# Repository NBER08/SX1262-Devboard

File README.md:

# SX1262 devboard for LoRa testing

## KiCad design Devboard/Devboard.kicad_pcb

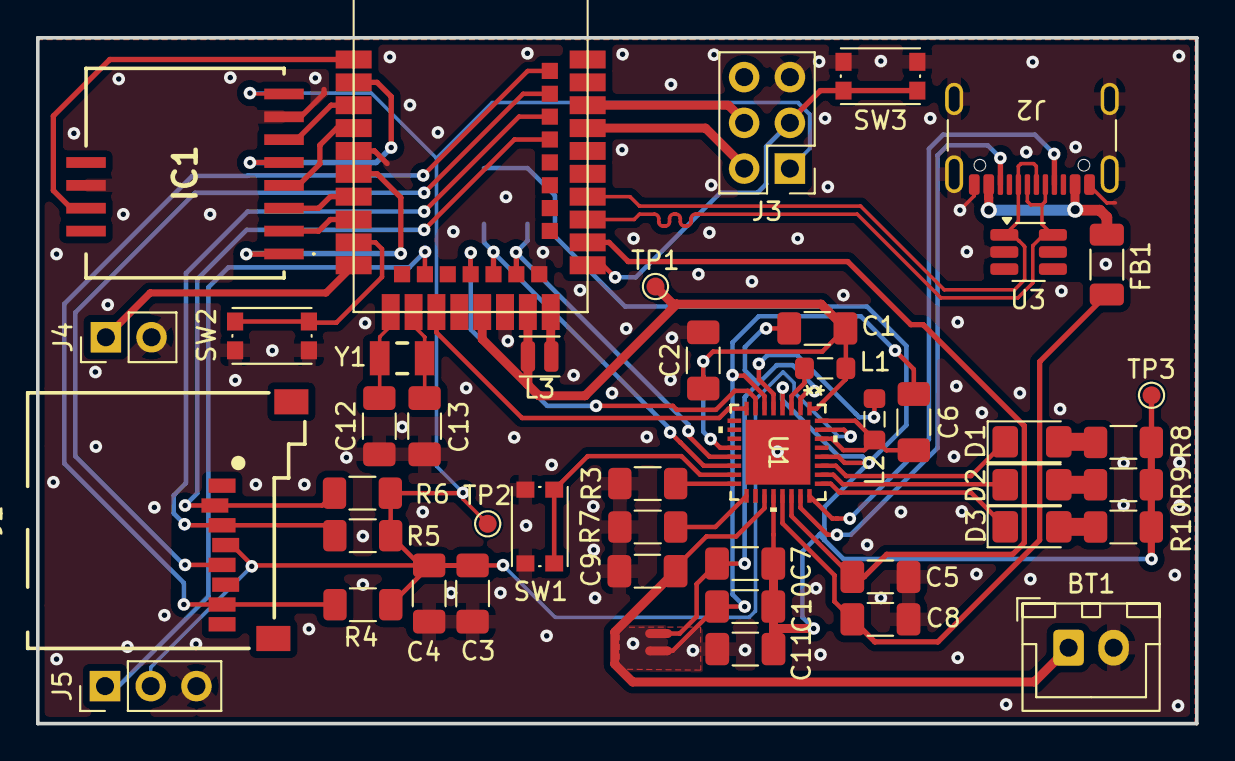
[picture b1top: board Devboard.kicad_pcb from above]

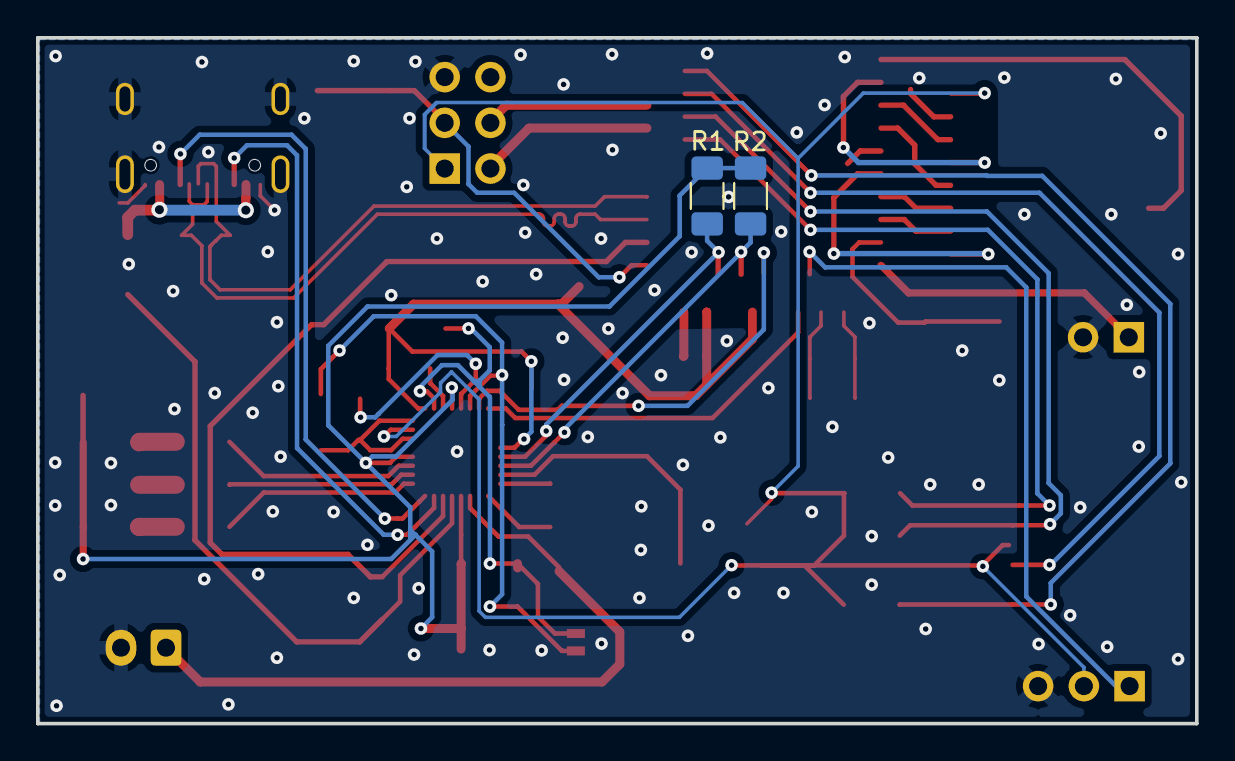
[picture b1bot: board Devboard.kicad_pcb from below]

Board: 2 copper layers, 64.4 x 38.1 mm, 49 parts (2 on the bottom side), 50 nets.

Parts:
BT1: 1S Lipo; JST_XH_B2B-XH-A_1x02_P2.50mm_Vertical
C1, C4, C6, C7, C10, C11: 10u; C_1206_3216Metric_Pad1.33x1.80mm_HandSolder
C2, C3: 0.1u; C_1206_3216Metric_Pad1.33x1.80mm_HandSolder
C5, C8: 1u; C_1206_3216Metric_Pad1.33x1.80mm_HandSolder
C9: 2u2; C_1206_3216Metric_Pad1.33x1.80mm_HandSolder
C12, C13: 22p; C_1206_3216Metric_Pad1.33x1.80mm_HandSolder
D1, D2, D3: Amber; LED_1206_3216Metric_Pad1.42x1.75mm_HandSolder
FB1: LI0603G121R-10; L_1206_3216Metric_Pad1.22x1.90mm_HandSolder
IC1: 114993390
J1: 693071010811
J2: USB_C_Receptacle_USB2.0_16P; USB_C_Receptacle_GCT_USB4105-xx-A_16P_TopMnt_Horizontal
J3: SWD; PinHeader_2x03_P2.54mm_Vertical
J4: RMF; PinHeader_1x02_P2.54mm_Vertical
J5: EXT_PIN; PinHeader_1x03_P2.54mm_Vertical
L1, L2: 2u2; L_0805_2012Metric_Pad1.05x1.20mm_HandSolder
L3: 10u(DNP); L_Changjiang_FTC201610D
NT1, NT2: NetTie_2; NetTie-2_SMD_Pad0.5mm
R1, R2: 4k7; R_1206_3216Metric_Pad1.30x1.75mm_HandSolder
R3: 150k; R_1206_3216Metric_Pad1.30x1.75mm_HandSolder
R4, R5, R6, R7: 47k; R_1206_3216Metric_Pad1.30x1.75mm_HandSolder
R8, R9, R10: 300; R_1206_3216Metric_Pad1.30x1.75mm_HandSolder
SW1: SHPHLD; SW_Push_1P1T_NO_CK_KMR2
SW2: SW_Push; SW_Push_1P1T_NO_CK_KMR2
SW3: RST; SW_Push_1P1T_NO_CK_KMR2
TP1: VMCU; TestPoint_Pad_D1.0mm
TP2: 3V3; TestPoint_Pad_D1.0mm
TP3: VSYS; TestPoint_Pad_D1.0mm
U1: NPM1304-QEAA-R; QFN32_5X5_NOR
U2: E73-2G4M08S1C
U3: SRV05-4; SOT-23-6_Handsoldering
Y1: 32.768; WE-XTAL_CFPX-217

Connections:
+3.3V: C3.2, C4.2, IC1.8 (VCC), J1.4 (VDD), J3.1, J5.2, R4.1, R5.1, R6.1, TP2.1 (1_1), U1.31 (LSOUT2/VOUTLDO2)
/PVSS1: C1.1, C7.1, NT1.2, U1.2 (PVSS1)
/PVSS2: C6.2, C10.1, NT2.2, U1.6 (PVSS2)
BM_INT: U1.8 (GPIO1), U2.15 (P0.05/AIN3)
BM_RST: U1.7 (GPIO0), U2.18 (P0.04/AIN2)
CC1: J2.A5 (CC1), U1.24 (CC2)
CC2: J2.B5 (CC2), U1.23 (CC1)
CS: J1.2 (CD/DAT3), R6.2, U2.36 (P1.00)
D+: J2.A6 (D+), J2.B6 (D+), U2.31 (DP), U3.1 (IO1)
D-: J2.A7 (D-), J2.B7 (D-), U2.29 (DM), U3.6 (IO4)
EXT_PIN: J5.1, U2.14 (P0.06)
GND: BT1.2 (-), C2.2, C3.1, C4.1, C5.1, C8.1, C9.1, C11.1, C12.1, C13.1, IC1.7 (GND_1), IC1.10 (GND_2), J2.A1 (GND), J2.A12 (GND), J2.B1 (GND), J2.B12 (GND), J2.SH, J3.5, J4.2, J5.3, NT1.1, NT2.1, R3.2, R7.2, SW1.2, SW2.2, SW3.2, U1.33 (AVSS), U2.5 (GND@1), U2.21 (GND@2), U2.24 (GND@3), U3.2 (VN)
LoRa_BUSY: IC1.11 (BUSY), U2.1 (P1.11)
LoRa_MISO: IC1.2 (MISO), U2.8 (P0.29/AIN5)
LoRa_MOSI: IC1.3 (MOSI), U2.7 (P0.02/AIN0)
LoRa_NSS: IC1.6 (NSS), U2.3 (P0.03/AIN1)
LoRa_RST: IC1.5 (NRST), U2.2 (P1.10)
LoRa_SCK: IC1.4 (SCK), U2.4 (P0.28/AIN4)
LoRa_SW: IC1.1 (RF_SW_), U2.6 (P1.13)
MISO: J1.7 (DAT0), R4.2, U2.42 (P1.06)
MOSI: J1.3 (CMD), R5.2, U2.38 (P1.02)
unnamed: D1.2 (A), R8.1
unnamed: D1.1 (K), U1.27 (LED2)
unnamed: D2.2 (A), R9.1
unnamed: D2.1 (K), U1.26 (LED1)
unnamed: D3.2 (A), R10.1
unnamed: D3.1 (K), U1.25 (LED0)
unnamed: FB1.1, J2.A4 (VBUS), J2.A9 (VBUS), J2.B4 (VBUS), J2.B9 (VBUS)
unnamed: C6.1, L2.1, U1.30 (LSIN2/VINLDO2), U1.32 (VOUT2)
unnamed: SW1.1, U1.15 (SHPHLD)
unnamed: L1.1, U1.3 (SW1)
unnamed: R7.1, U1.17 (VSET1)
unnamed: R3.1, U1.16 (VSET2)
unnamed: L3.1, U2.25 (DCCH)
unnamed: C12.2, U2.11 (P0.00/XL1), Y1.2
unnamed: C13.2, U2.13 (P0.01/XL2), Y1.1
RMF: J4.1, U2.10 (P0.30/AIN6)
RST: J3.3, SW3.1, U2.26 (P0.18/RESET)
SCK: J1.5 (CLK), U2.40 (P1.04)
SCL: R2.1, U1.14 (SCL), U2.20 (P0.12)
SDA: R1.1, U1.13 (SDA), U2.22 (P0.07)
SW0: SW2.1, U2.9 (P0.31/AIN7)
SW2: L2.2, U1.5 (SW2)
SWDCLK: J3.4, U2.39 (SWDCLK)
SWDIO: J3.2, U2.37 (SWDIO)
VBAT: BT1.1 (+), C9.2, U1.19 (VBAT)
VBUS: C8.2, FB1.2, U1.21 (VBUS)
VBUSOUT: C5.2, U1.22 (VBUSOUT), U2.27 (VBUS)
VMCU: C1.2, C2.1, L1.2, L3.2, TP1.1 (1_1), U1.1 (VOUT1), U1.12 (VDDIO), U2.19 (VDD), U2.23 (VDDH)
VSYS: C7.2, C10.2, C11.2, R1.2, R2.2, R8.2, R9.2, R10.2, TP3.1 (1_1), U1.4 (PVDD), U1.20 (VSYS), U1.28 (LSIN1/VINLDO1)

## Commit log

2026-05-30 Update README to reflect SX1262 devboard
2026-05-31 added sd card, and refined design
2026-06-03 added gitignore
2026-06-04 Added external pin
2026-06-04 Added 3V3 output
2026-06-04 Final commit
2026-06-09 Removed backups folder
